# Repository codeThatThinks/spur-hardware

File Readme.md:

# spur-hardware

A physical UEFI boot switch -- PCB design files.

## Theory of Operation

Spur appears as a virtual USB mass storage device and acts as a first-stage UEFI bootloader. This bootloader loads a specific boot entry in the system UEFI table depending on the position of a physical switch on the device.

A 1MB SPI NOR flash chip contains the FAT32 filesystem on which the UEFI bootloader lives. An STM32F4 microcontroller provides read/write access to the flash over USB. In addition, it presents a virtual file which is read by the bootloader to determine the state of the physical switch.

## License

The MIT License

Copyright 2020 Ian Glen

Permission is hereby granted, free of charge, to any person obtaining a copy of this software and associated documentation files (the "Software"), to deal in the Software without restriction, including without limitation the rights to use, copy, modify, merge, publish, distribute, sublicense, and/or sell copies of the Software, and to permit persons to whom the Software is furnished to do so, subject to the following conditions:

The above copyright notice and this permission notice shall be included in all copies or substantial portions of the Software.

THE SOFTWARE IS PROVIDED "AS IS", WITHOUT WARRANTY OF ANY KIND, EXPRESS OR IMPLIED, INCLUDING BUT NOT LIMITED TO THE WARRANTIES OF MERCHANTABILITY, FITNESS FOR A PARTICULAR PURPOSE AND NONINFRINGEMENT. IN NO EVENT SHALL THE AUTHORS OR COPYRIGHT HOLDERS BE LIABLE FOR ANY CLAIM, DAMAGES OR OTHER LIABILITY, WHETHER IN AN ACTION OF CONTRACT, TORT OR OTHERWISE, ARISING FROM, OUT OF OR IN CONNECTION WITH THE SOFTWARE OR THE USE OR OTHER DEALINGS IN THE SOFTWARE.

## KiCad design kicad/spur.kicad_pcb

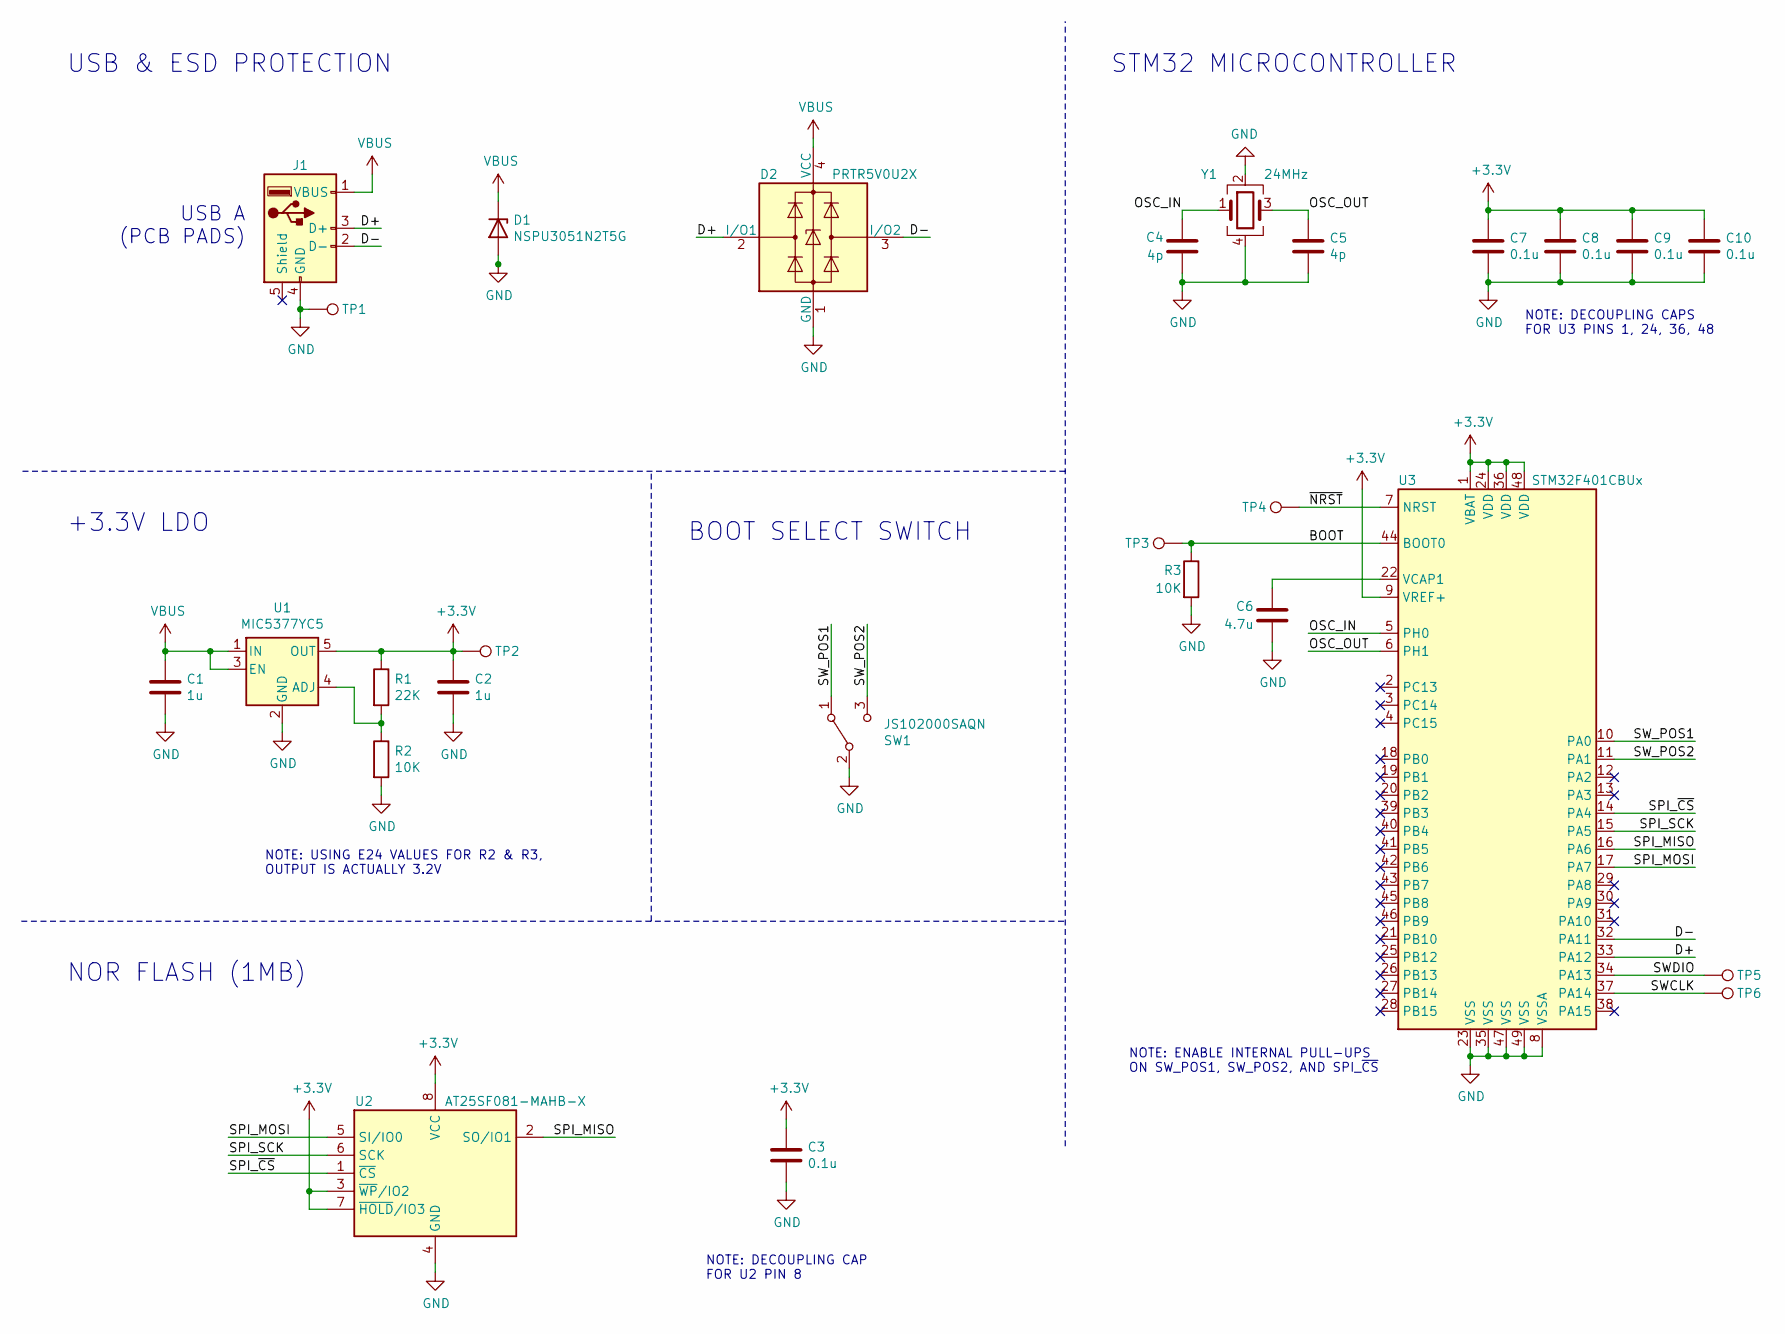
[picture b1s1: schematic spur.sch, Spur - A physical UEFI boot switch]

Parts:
C1, C2: 1u; C_0402_1005Metric
C3, C7, C8, C9, C10: 0.1u; C_0402_1005Metric
C4, C5: 4p; C_0402_1005Metric
C6: 4.7u; C_0402_1005Metric
D1: NSPU3051N2T5G; D_0402_1005Metric
D2: PRTR5V0U2X; SOT-886
J1: USB_A; USB_A_pads
R1: 22K; R_0402_1005Metric
R2, R3: 10K; R_0402_1005Metric
SW1: JS102000SAQN; SW_SPDT_CK-JS102000SAQN
TP1: GND; TestPoint_Pad_D1.0mm
TP2: 3V3; TestPoint_Pad_D1.0mm
TP3: BOOT; TestPoint_Pad_D1.0mm
TP4: NRST; TestPoint_Pad_D1.0mm
TP5: SWDIO; TestPoint_Pad_D1.0mm
TP6: SWCLK; TestPoint_Pad_D1.0mm
U1: MIC5377YC5; SOT-353_SC-70-5
U2: AT25SF081-MAHB-X; SON-8-1EP_3x2mm_P0.5mm_EP0.2x1.6mm
U3: STM32F401CBUx; QFN-48-1EP_7x7mm_P0.5mm_EP5.6x5.6mm
Y1: 24MHz; Crystal_SMD_2016-4Pin_2.0x1.6mm

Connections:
+3V3: C2.1, C3.1, C7.1, C8.1, C9.1, C10.1, R1.1, TP2.1, U1.5 (OUT), U2.3 (~WP~/IO2), U2.7 (~HOLD~/IO3), U2.8 (VCC), U3.1 (VBAT), U3.9 (VREF+), U3.24 (VDD), U3.36 (VDD), U3.48 (VDD)
/BOOT: R3.1, TP3.1, U3.44 (BOOT0)
/D+: D2.2 (I/O1), J1.3 (D+), U3.33 (PA12)
/D-: D2.3 (I/O2), J1.2 (D-), U3.32 (PA11)
/OSC_IN: C4.1, U3.5 (PH0), Y1.1
/OSC_OUT: C5.1, U3.6 (PH1), Y1.3
/SPI_MISO: U2.2 (SO/IO1), U3.16 (PA6)
/SPI_MOSI: U2.5 (SI/IO0), U3.17 (PA7)
/SPI_SCK: U2.6 (SCK), U3.15 (PA5)
/SPI_~CS: U2.1 (~CS), U3.14 (PA4)
/SWCLK: TP6.1, U3.37 (PA14)
/SWDIO: TP5.1, U3.34 (PA13)
/SW_POS1: SW1.1 (A), U3.10 (PA0)
/SW_POS2: SW1.3 (C), U3.11 (PA1)
/~NRST: TP4.1, U3.7 (NRST)
GND: C1.2, C2.2, C3.2, C4.2, C5.2, C6.2, C7.2, C8.2, C9.2, C10.2, D1.2 (A), D2.1 (GND), J1.4 (GND), R2.2, R3.2, SW1.2 (B), TP1.1, U1.2 (GND), U2.4 (GND), U3.8 (VSSA), U3.23 (VSS), U3.35 (VSS), U3.47 (VSS), U3.49 (VSS), Y1.2, Y1.4
unnamed: C6.1, U3.22 (VCAP1)
unnamed: R1.2, R2.1, U1.4 (ADJ)
VBUS: C1.1, D1.1 (K), D2.4 (VCC), J1.1 (VBUS), U1.1 (IN), U1.3 (EN)

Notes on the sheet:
USB A (PCB PADS)
USB & ESD PROTECTION
STM32 MICROCONTROLLER
NOR FLASH (1MB)
+3.3V LDO
BOOT SELECT SWITCH
NOTE: DECOUPLING CAP FOR U2 PIN 8
NOTE: DECOUPLING CAPS FOR U3 PINS 1, 24, 36, 48
NOTE: USING E24 VALUES FOR R2 & R3, OUTPUT IS ACTUALLY 3.2V
NOTE: ENABLE INTERNAL PULL-UPS ON SW_POS1, SW_POS2, AND SPI_~CS

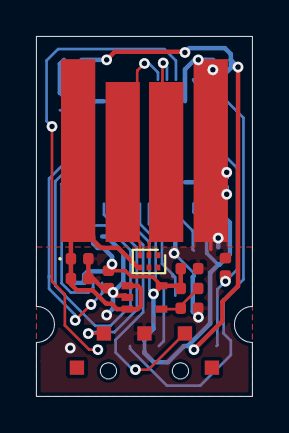
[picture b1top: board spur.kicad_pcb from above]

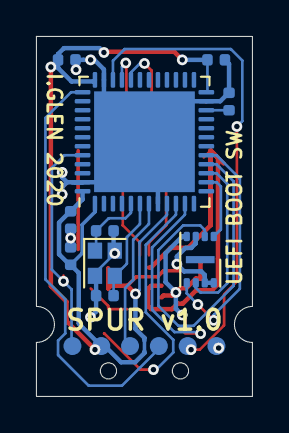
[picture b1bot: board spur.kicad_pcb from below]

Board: 2 copper layers, 12.0 x 20.0 mm, 27 parts (16 on the bottom side), 19 nets.

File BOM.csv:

Spur v1.0 BOM,,,,,,,,,,,
Qty.,Refdes,Description,Value,Package,Manufacturer,Manufacturer P/N,Digikey P/N,Unit Price @ Qty 1,Price @ Qty 1,Unit Price @ Qty 100,Price @ Qty 100
2,"C1, C2","Capacitor, ceramic, 6.3V",1u,0402,Samsung,CL05A105KQ5NNNC,1276-1010-1-ND,$0.10000,$0.20,$0.00870,$0.02
5,"C3, C7, C8, C9, C10","Capacitor, ceramic, 6.3V",0.1u,0402,Samsung,CL05A104KQ5NNNC,1276-1442-1-ND,$0.10000,$0.50,$0.00850,$0.04
2,"C4, C5","Capacitor, ceramic, 50V",4p,0402,Yageo,CC0402BRNPO9BN4R0,311-3705-1-ND,$0.10000,$0.20,$0.01760,$0.04
1,C6,"Capacitor, ceramic, 10V",4.7u,0402,Samsung,CL05A475MP5NRNC,1276-1482-1-ND,$0.10000,$0.10,$0.00336,$0.00
1,D1,"Zener diode, ESD",,0402,ON Semi,NSPU3051N2T5G,NSPU3051N2T5GOSCT-ND,$0.36000,$0.36,$0.13440,$0.13
1,D2,"Diode array, ESD, 2 channel",,SOT-886,Nexperia,"PRTR5V0U2F,115",1727-4161-1-ND,$0.49000,$0.49,$0.25500,$0.26
1,PCB1,"Bare PCB, 2 layer, 0.6mm, 1oz, ENIG",,,JLCPCB,,,$3.60000,$3.60,$0.49500,$0.50
2,"R2, R3","Resistor, thick film, 1%, 1/16W",10K,0402,Yageo,RC0402FR-0710KL,311-10.0KLRCT-ND,$0.10000,$0.20,$0.00580,$0.01
1,R1,"Resistor, thick film, 1%, 1/16W",23K,0402,Yageo,RC0402FR-0722KL,311-22.0KLRCT-ND,$0.10000,$0.10,$0.00580,$0.01
1,SW1,"Slide switch, SPDT",,JS102000SAQN,C&K,JS102000SAQN,401-2005-1-ND,$0.71000,$0.71,$0.56960,$0.57
1,U1,"Linear regulator, adjustable, 150mA",,SOT-353,Microchip,MIC5377YC5-TR,576-3358-1-ND,$0.26000,$0.26,$0.20000,$0.20
1,U2,"Flash memory, NOR, SPI, 1MiB",,8-UDFN,Adesto,AT25SF081B-MAHB-T,1265-AT25SF081B-MAHB-TCT-ND,$0.40000,$0.40,$0.32560,$0.33
1,U3,"Microcontroller, 128KiB flash",,48-UFQFN,STmicro,STM32F401CBU6,497-17425-ND,$4.96000,$4.96,$3.64690,$3.65
1,Y1,"Crystal, 24MHz, Cl=12pF",,4-SMD,Murata,XRCGB24M000F1H03R0,490-18289-1-ND,$0.44000,$0.44,$0.29100,$0.29
,,,,,,,,Price @ Qty 1:,$12.52,Price @ Qty 100:,$6.03

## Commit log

2020-09-22 Remove UART test points
2020-09-23 Move switch input pins
2020-09-25 Update R2 value, fix C1 & C2 symbols, improve schematic notes
2020-09-25 Add passives to BOM
2020-09-25 Add PCB to BOM
2020-09-27 Switch to internal pull-ups, remove 4.7uF bulk cap
2020-09-27 Remove pull-ups, bulk cap from BOM
2020-09-30 Add custom footprint for flash chip
2020-12-04 Add PCB layout
